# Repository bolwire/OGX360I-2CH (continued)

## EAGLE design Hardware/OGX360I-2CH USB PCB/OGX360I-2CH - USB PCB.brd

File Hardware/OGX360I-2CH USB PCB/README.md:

# OGX360I-2CH USB PCB.
This board was designed using [Autodesk Eagle](https://www.autodesk.com/products/eagle/overview). You can edit the `.brd` and `.sch` with this program.

## Printed Circuit Board
When fabricating your own, you can download the premade gerbers or generate your own. Suggested PCB properties are:  <br>
*2 layers, 19x42mm, 1.6mm thick, HASL, 1oz copper, no castellated holes, any colour you want!*<br>

## Bill of Materials
All the passive components listed (Resistors, capacitors etc) are listed for reference only. Any equivalents you find would be suitable. Use your best judgement. 
You should check this list against the schematic to ensure nothing is missed.  
**Digikey Quick Cart: http://www.digikey.com/short/zw017j**  

| Qty | Value/Model | Description | Marking | URL (Passive components provided as sample only) |
| --- | --- | --- | --- | --- |
| 1 | RC0805JR-0791RL | RES SMD 91 OHM 5% 1/8W 0805 | R1 | https://www.digikey.com/product-detail/en/yageo/RC0805JR-0791RL/311-91ARCT-ND/731331 |
| 1 | AU-Y1006 | CONN RCPT USB1.1 TYPEA 4P SMD RA | USB | https://www.digikey.com/product-detail/en/assmann-wsw-components/AU-Y1006/AE11182-ND/278927 |
| 1 | PCM12SMTR | SWITCH SLIDE SPDT 300MA 6V | SW1 | https://www.digikey.com/product-detail/en/c-k/PCM12SMTR/401-2016-1-ND/1640125 |
| 1 | SM06B-SRSS-TB(LF)(SN) | CONN HEADER SMD R/A 6POS 1MM | CONN / J1 | https://www.digikey.com/product-detail/en/jst-sales-america-inc/SM06B-SRSS-TB-LF-SN/455-1806-1-ND/926877 |
| 1 | A06SR06SR30K254A | JUMPER 06SR-3S - 06SR-3S 10" | CABLE | https://www.digikey.com/product-detail/en/jst-sales-america-inc/A06SR06SR30K254A/455-3647-ND/9922197 |
| 1 | 150080GS75000 | LED GREEN CLEAR 0805 SMD | LED | https://www.digikey.com/product-detail/en/w-rth-elektronik/150080GS75000/732-4983-1-ND/4489913 |

## Assembled Photo (coming soon)

By KingLuxor

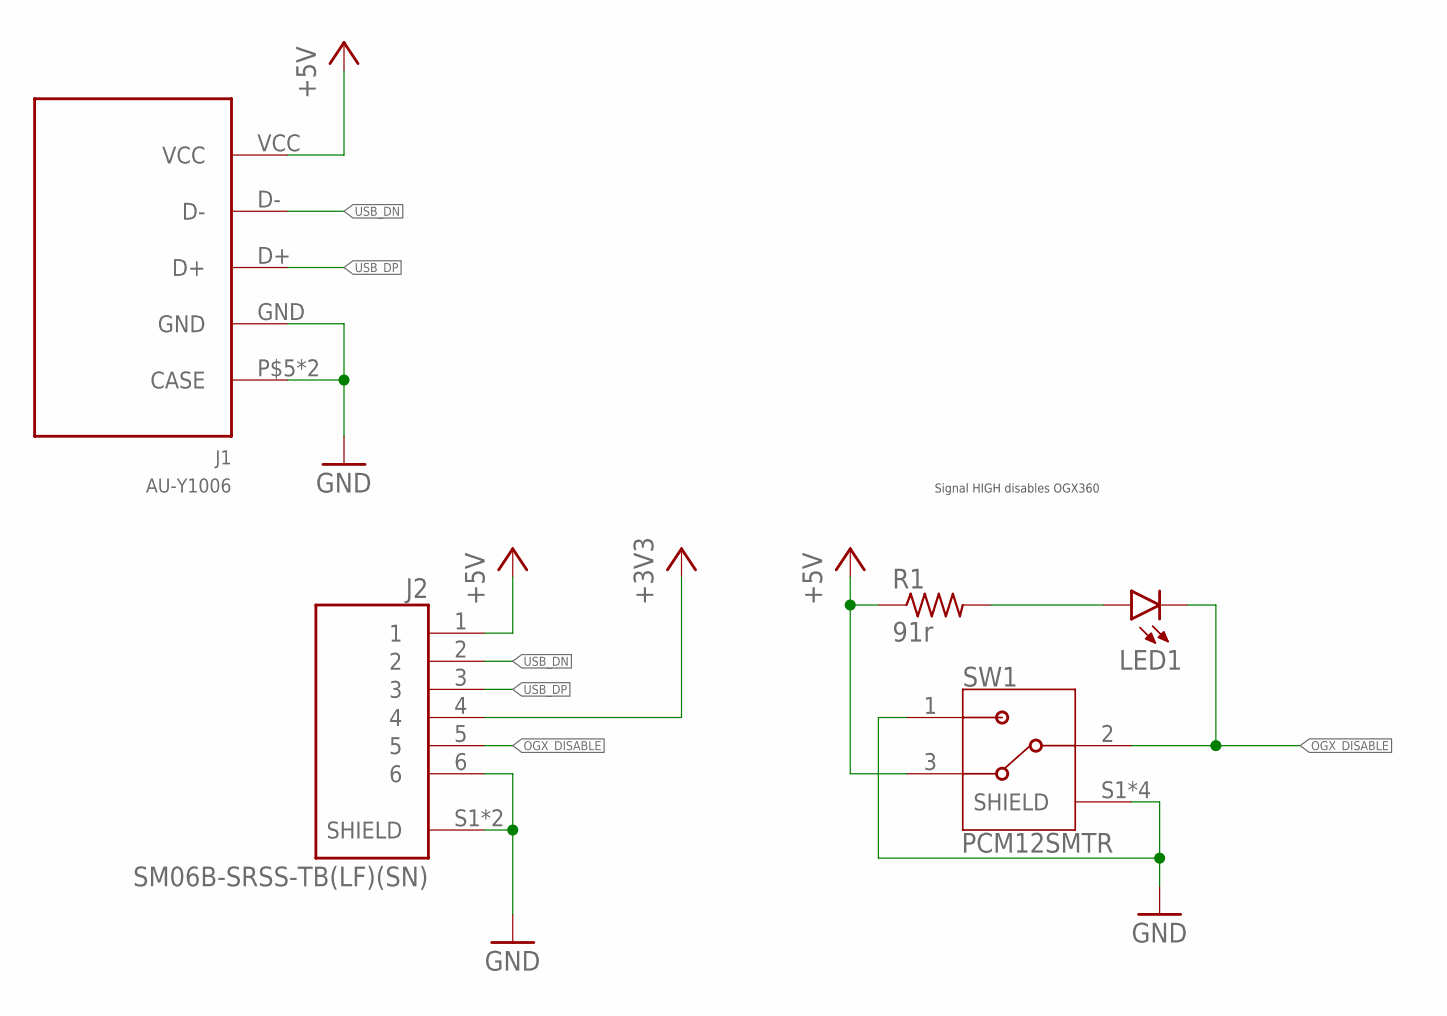
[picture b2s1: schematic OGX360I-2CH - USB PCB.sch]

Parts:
J1: AU-Y1006; USBA_SMD
J2: SM06B-SRSS-TB(LF)(SN); JST_SM06B-SRSS-TB(LF)(SN)
LED1: LEDCHIP-LED0805; CHIP-LED0805
R1: 91r; R0805
SW1: PCM12SMTR; SW_PCM12SMTR

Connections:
+3V3: J2.4
+5V: J1.VCC, J2.1, R1.1, SW1.3
GND: J1.GND, J1.P$5 (CASE), J1.P$6 (CASE), J2.6, J2.S1 (SHIELD), J2.S2 (SHIELD), SW1.1, SW1.S1 (SHIELD), SW1.S2 (SHIELD), SW1.S3 (SHIELD), SW1.S4 (SHIELD)
unnamed: LED1.A, R1.2
OGX_DISABLE: J2.5, LED1.C, SW1.2
USB_DN: J1.D-, J2.2
USB_DP: J1.D+, J2.3

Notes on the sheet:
Signal HIGH disables OGX360

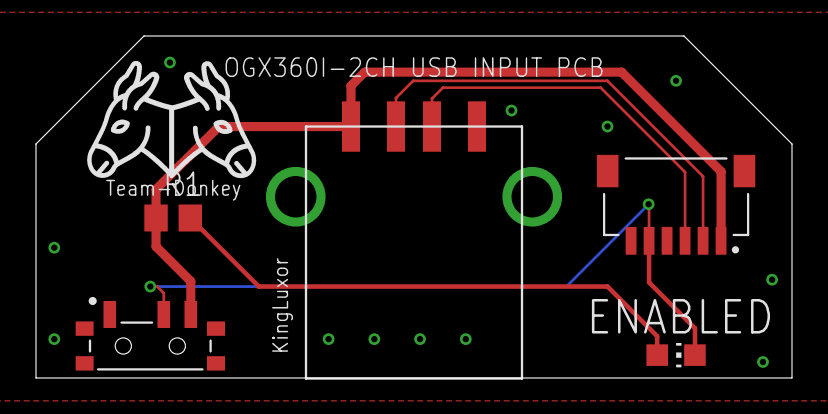
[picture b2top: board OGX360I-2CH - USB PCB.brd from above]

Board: 2 copper layers, 42.0 x 19.0 mm, 5 parts (0 on the bottom side), 6 nets.

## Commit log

2020-10-04 Initial commit (see extended)
    The files contained within this repo should be considered to be in the prototype stage of verification until you have verified them yourself or I have made a commit stating otherwise.
2020-10-06 Add images/readme for main pcb
2020-10-06 FIx readme location for main pcb
2020-10-06 Fix main PCB BOM table
2020-10-09 Add README.md to USB PCB
2020-10-18 Add .stl files for 3d printed case
